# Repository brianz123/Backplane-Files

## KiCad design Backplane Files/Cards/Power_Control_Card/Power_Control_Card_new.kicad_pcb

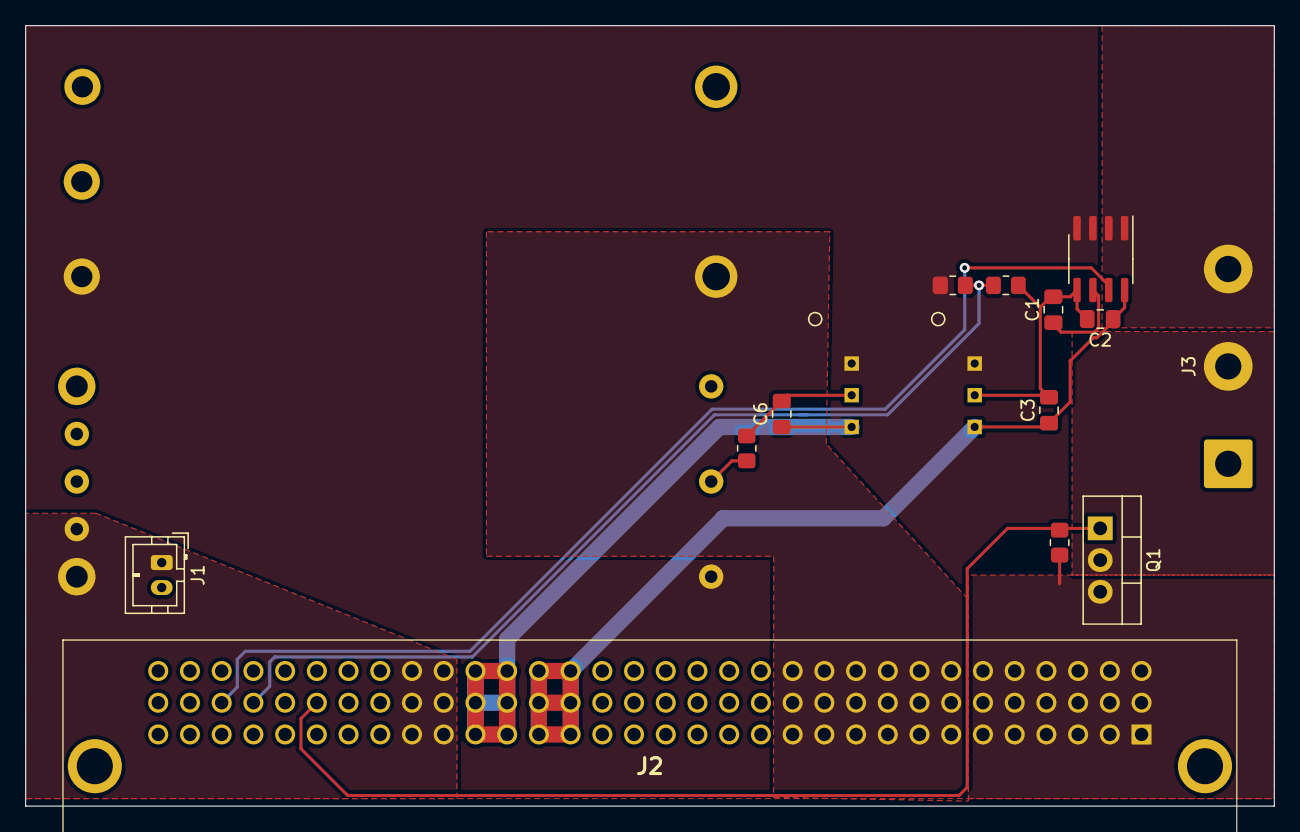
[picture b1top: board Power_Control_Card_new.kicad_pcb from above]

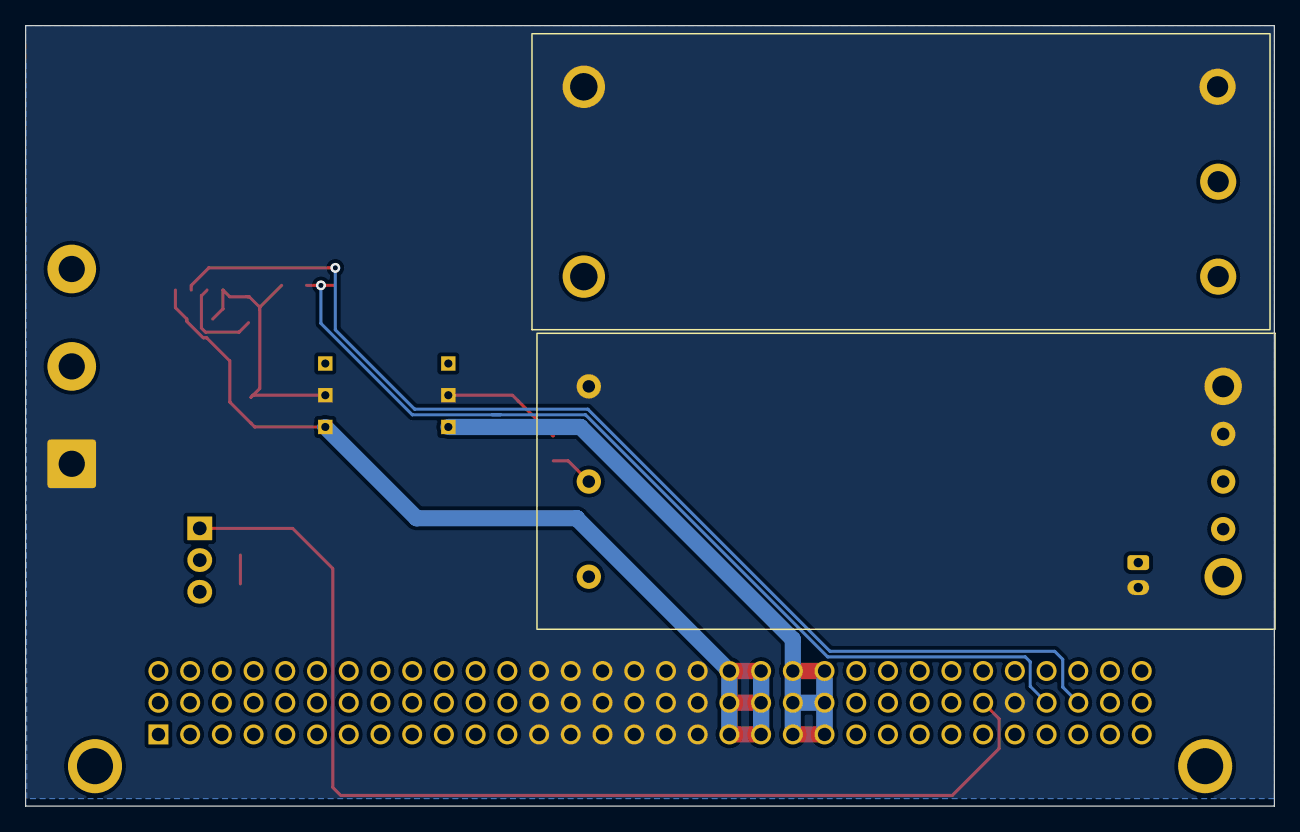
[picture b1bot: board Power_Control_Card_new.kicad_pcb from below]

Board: 2 copper layers, 100.0 x 62.5 mm, 17 parts (2 on the bottom side), 14 nets.

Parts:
C1: 47n; C_0805_2012Metric_Pad1.18x1.45mm_HandSolder
C2: 0.1u; C_0805_2012Metric_Pad1.18x1.45mm_HandSolder
C3, C6: 1u; C_0805_2012Metric_Pad1.18x1.45mm_HandSolder
DC/DC_CNVRT1: TSR2-2450; TSR2
DC/DC_CNVRT2: TSR2-2433; TSR2
INPT_CRRNT_SNSR1: TMCS1101A4B; SOIC-8_3.9x4.9mm_P1.27mm
J1: Conn_01x02; JST_PH_B2B-PH-K_1x02_P2.00mm_Vertical
J2: 6509475
J3: Conn_01x03_Pin; SolderWire-1.5sqmm_1x03_P7.8mm_D1.7mm_OD3.9mm
Q1: FQPF27P06; TO-220-3_Vertical
RSW1, RSW2: 10kO; R_0805_2012Metric_Pad1.20x1.40mm_HandSolder
U1: 240W_CONV
U2: 72W_CONV
VDIV1(R)1: 90kO; R_0805_2012Metric_Pad1.20x1.40mm_HandSolder
VDIV2(R)1: 10kO; R_0805_2012Metric_Pad1.20x1.40mm_HandSolder

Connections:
12V_Jetson: J1.1, J2.A23, J2.A24, J2.B23, J2.B24, J2.C23, J2.C24, U2.7 (SENSE+), U2.8 (VOUT)
+3.3V: C6.1, DC/DC_CNVRT2.3 (+V_OUT), J2.A21, J2.A22, J2.B21, J2.B22, J2.C21, J2.C22
+5V: C2.1, C3.1, DC/DC_CNVRT1.3 (+V_OUT), INPT_CRRNT_SNSR1.8 (VCC), J2.A19, J2.A20, J2.B19, J2.B20, J2.C19, J2.C20
+12V: J2.A7, J2.A8, J2.A9, J2.A10, J2.A11, J2.A12, J2.B7, J2.B8, J2.B9, J2.B10, J2.B11, J2.B12, J2.C7, J2.C8, J2.C9, J2.C10, J2.C11, J2.C12, U1.8 (VOUT)
+24V: J2.A1, J2.A2, J2.A3, J2.A4, J2.A5, J2.A6, J2.B1, J2.B2, J2.B3, J2.B4, J2.B5, J2.B6, J2.C1, J2.C2, J2.C3, J2.C4, J2.C5, J2.C6, Q1.3 (S), RSW1.1
/VBATT: INPT_CRRNT_SNSR1.1 (IP+), J3.3
/V_POWER: DC/DC_CNVRT1.1 (+V_IN), DC/DC_CNVRT2.1 (+V_IN), INPT_CRRNT_SNSR1.3 (IP-), U1.1 (VIN), U2.1 (VIN), VDIV1(R)1.1
DAT1: J2.B29, VDIV1(R)1.2, VDIV2(R)1.1
DAT2: INPT_CRRNT_SNSR1.7 (VIOUT), J2.B30
unnamed: C1.1, INPT_CRRNT_SNSR1.6 (FILTER)
unnamed: J3.2, Q1.2 (D)
unnamed: RSW2.1, U2.2 (ON/OFF)
SW1: C1.2, C2.2, C3.2, C6.2, DC/DC_CNVRT1.2 (GND), DC/DC_CNVRT2.2 (GND), INPT_CRRNT_SNSR1.5 (GND), J1.2, J2.A13, J2.A14, J2.A15, J2.A16, J2.A17, J2.A18, J2.B13, J2.B14, J2.B15, J2.B16, J2.B17, J2.B18, J2.B28, J2.C13, J2.C14, J2.C15, J2.C16, J2.C17, J2.C18, J3.1, RSW2.2, U1.3 (IN-), U1.4 (OUT-), U2.3 (IN-), U2.4 (OUT-), U2.5 (SENSE-), VDIV2(R)1.2
SW2: J2.B27, Q1.1 (G), RSW1.2

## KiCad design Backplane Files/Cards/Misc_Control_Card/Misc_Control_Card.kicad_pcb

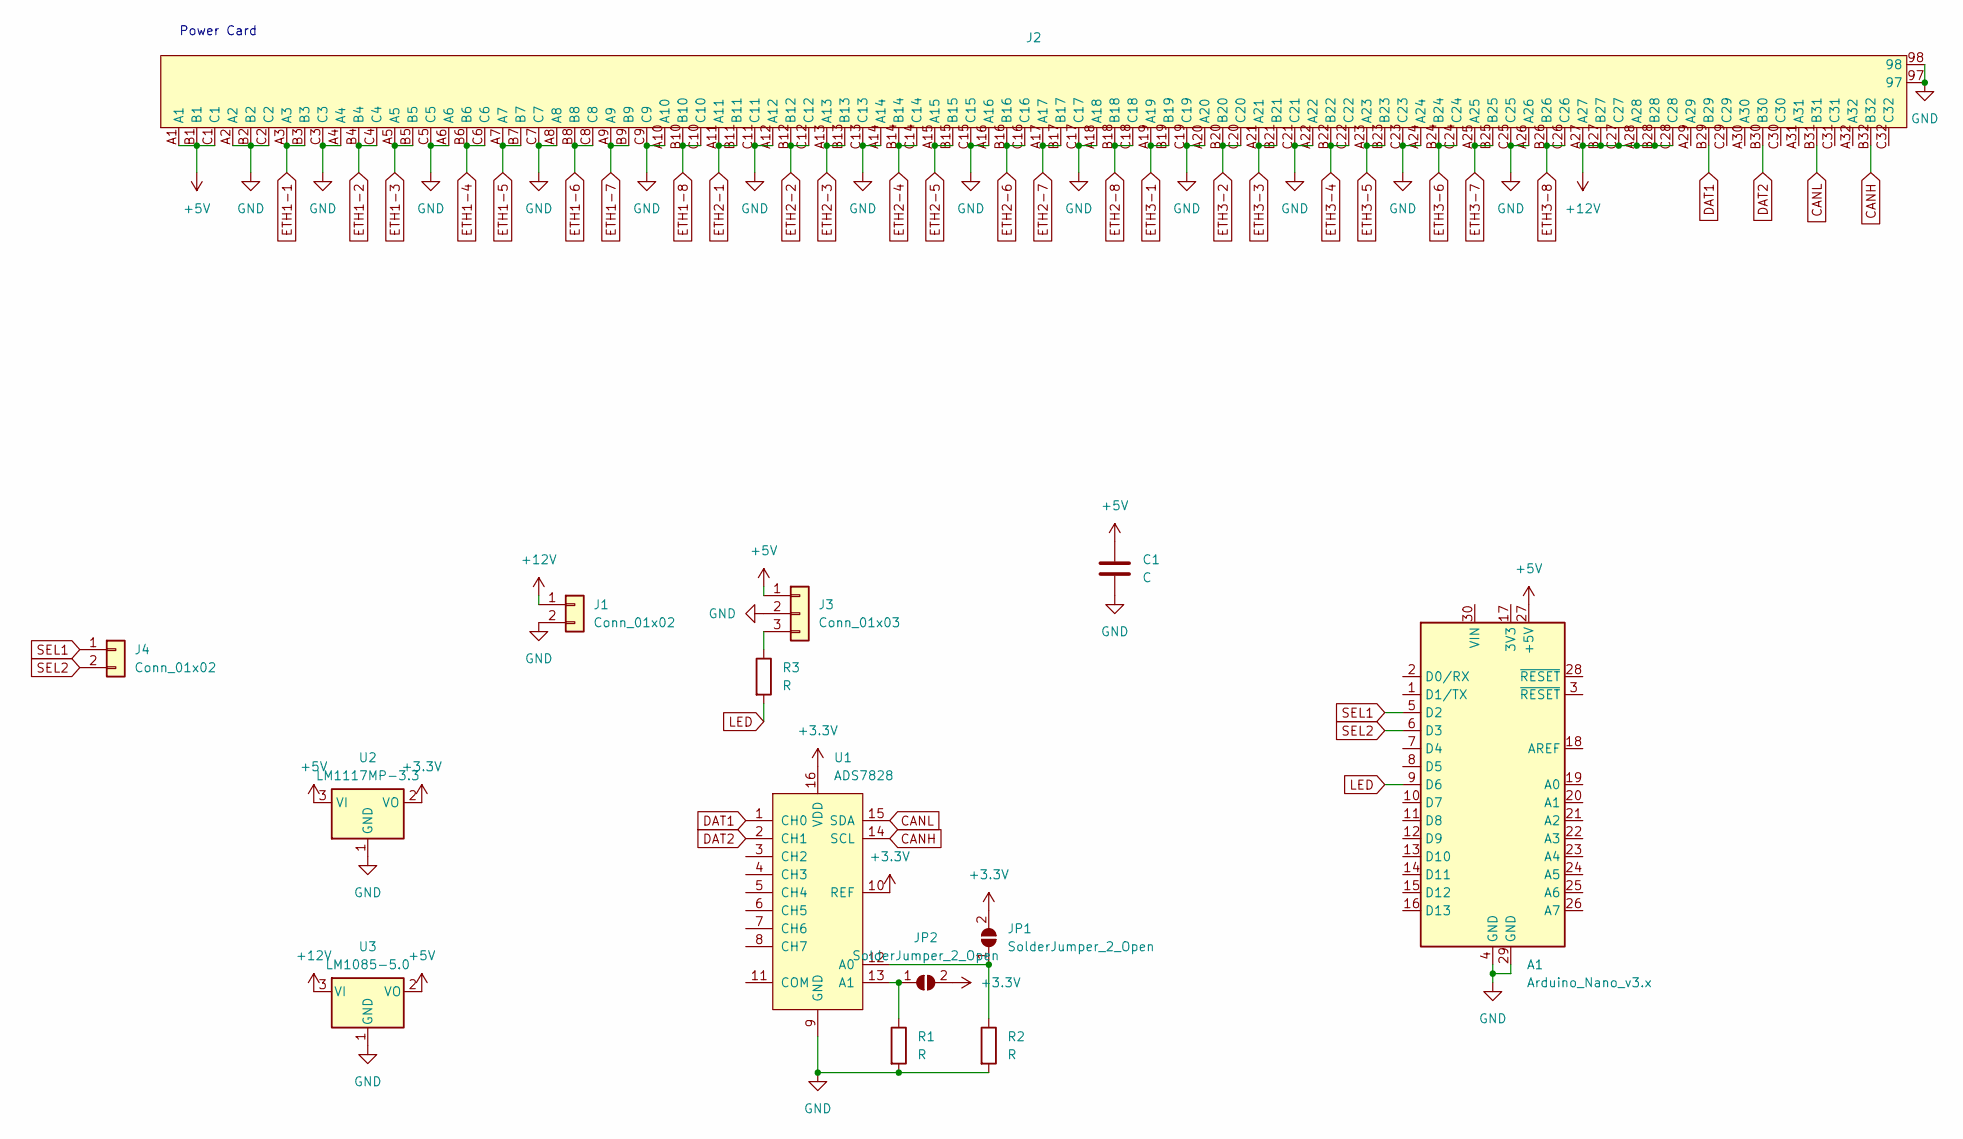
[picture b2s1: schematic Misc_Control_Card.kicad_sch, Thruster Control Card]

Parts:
A1: Arduino_Nano_v3.x; Arduino_Nano
C1: C; CP_Radial_D6.3mm_P2.50mm
J1, J4: Conn_01x02; PinHeader_1x02_P2.54mm_Vertical
J2: 6509475
J3: Conn_01x03; PinHeader_1x03_P2.54mm_Vertical
JP1, JP2: SolderJumper_2_Open; SolderJumper-2_P1.3mm_Open_TrianglePad1.0x1.5mm
R1, R2, R3: R; R_0805_2012Metric_Pad1.20x1.40mm_HandSolder
U1: ADS7828; TSSOP-16_4.4x5mm_P0.65mm
U2: LM1117MP-3.3; SOT-223-3_TabPin2
U3: LM1085-5.0; TO-220-3_Vertical

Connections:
+3.3V: JP1.2 (B), JP2.2 (B), U1.10 (REF), U1.16 (VDD), U2.2 (VO)
+5V: A1.27 (+5V), C1.1, J2.A1, J2.B1, J2.C1, J3.1, U2.3 (VI), U3.2 (VO)
+12V: J1.1, J2.A27, J2.A28, J2.B27, J2.B28, J2.C27, J2.C28, U3.3 (VI)
CANH: J2.B32, U1.14 (SCL)
CANL: J2.B31, U1.15 (SDA)
DAT1: J2.B29, U1.1 (CH0)
DAT2: J2.B30, U1.2 (CH1)
ETH1-1: J2.A3, J2.B3
ETH1-2: J2.B4, J2.C4
ETH1-3: J2.A5, J2.B5
ETH1-4: J2.B6, J2.C6
ETH1-5: J2.A7, J2.B7
ETH1-6: J2.B8, J2.C8
ETH1-7: J2.A9, J2.B9
ETH1-8: J2.B10, J2.C10
ETH2-1: J2.A11, J2.B11
ETH2-2: J2.B12, J2.C12
ETH2-3: J2.A13, J2.B13
ETH2-4: J2.B14, J2.C14
ETH2-5: J2.A15, J2.B15
ETH2-6: J2.B16, J2.C16
ETH2-7: J2.A17, J2.B17
ETH2-8: J2.B18, J2.C18
ETH3-1: J2.A19, J2.B19
ETH3-2: J2.B20, J2.C20
ETH3-3: J2.A21, J2.B21
ETH3-4: J2.B22, J2.C22
ETH3-5: J2.A23, J2.B23
ETH3-6: J2.B24, J2.C24
ETH3-7: J2.A25, J2.B25
ETH3-8: J2.B26, J2.C26
GND: A1.4 (GND), A1.29 (GND), C1.2, J1.2, J2.97, J2.98, J2.A2, J2.A4, J2.A6, J2.A8, J2.A10, J2.A12, J2.A14, J2.A16, J2.A18, J2.A20, J2.A22, J2.A24, J2.A26, J2.B2, J2.C2, J2.C3, J2.C5, J2.C7, J2.C9, J2.C11, J2.C13, J2.C15, J2.C17, J2.C19, J2.C21, J2.C23, J2.C25, J3.2, R1.2, R2.2, U1.9 (GND), U2.1 (GND), U3.1 (GND)
LED: A1.9 (D6), R3.2
unnamed: J3.3, R3.1
unnamed: JP1.1 (A), R2.1, U1.12 (A0)
unnamed: JP2.1 (A), R1.1, U1.13 (A1)
SEL1: A1.5 (D2), J4.1
SEL2: A1.6 (D3), J4.2

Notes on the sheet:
Power Card

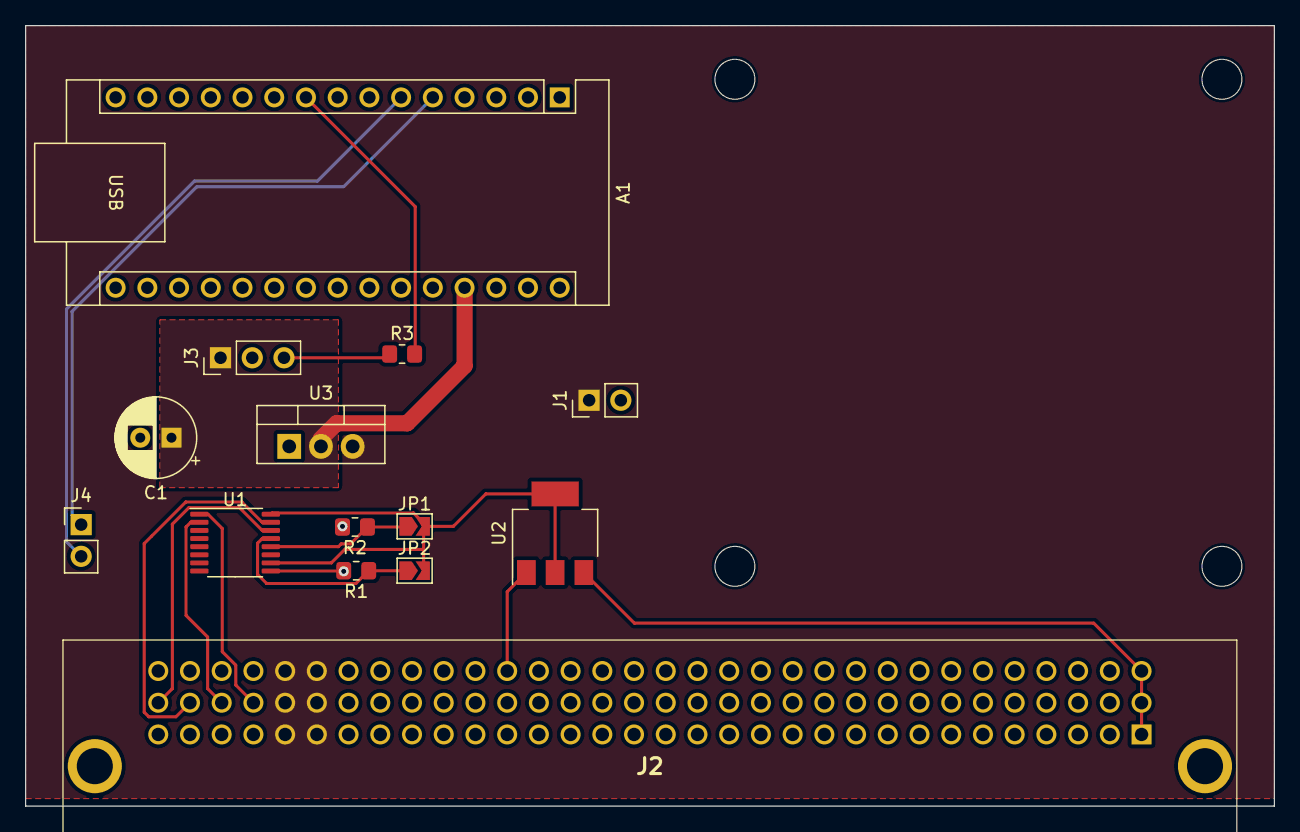
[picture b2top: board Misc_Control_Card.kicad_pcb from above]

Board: 2 copper layers, 100.0 x 62.5 mm, 14 parts (0 on the bottom side), 38 nets.

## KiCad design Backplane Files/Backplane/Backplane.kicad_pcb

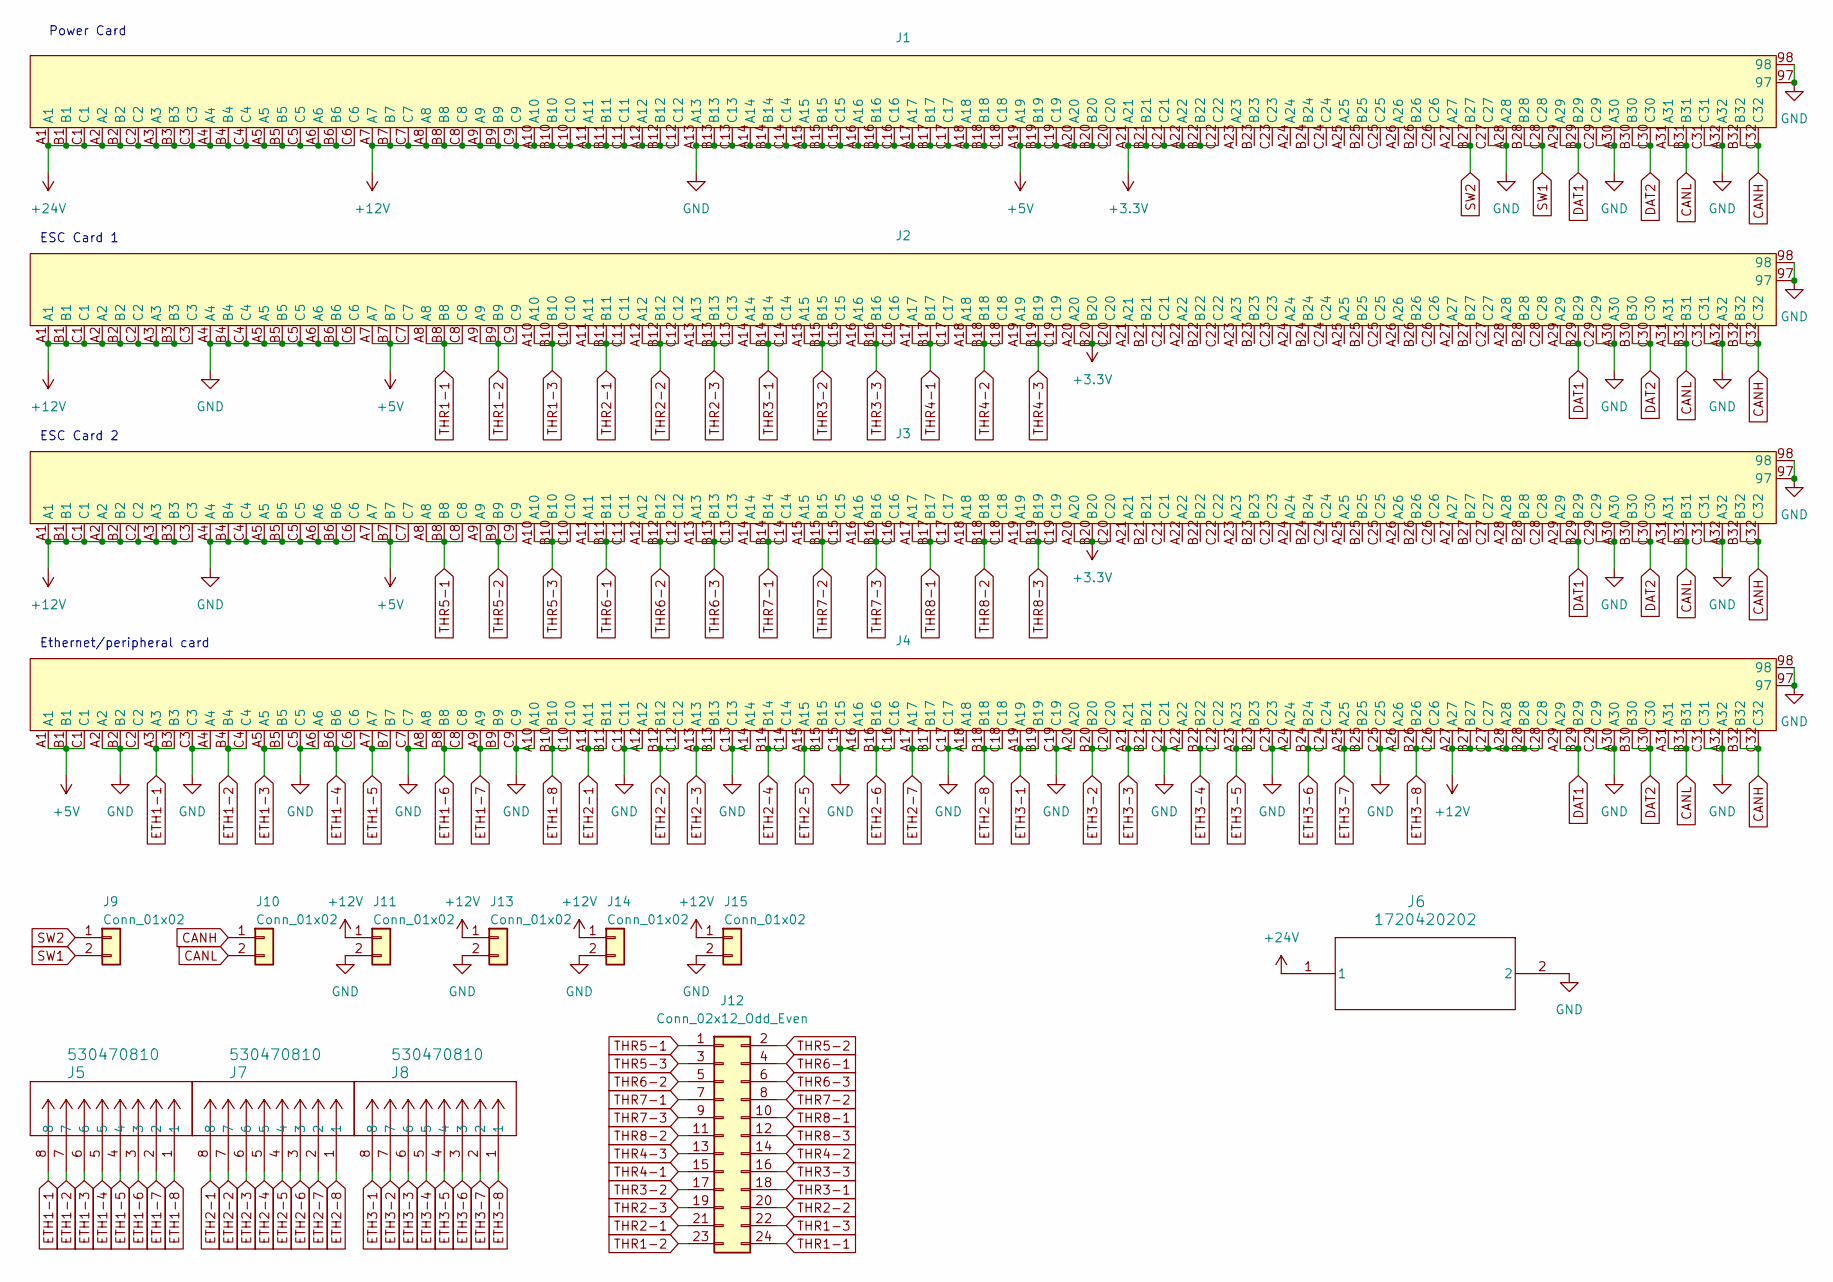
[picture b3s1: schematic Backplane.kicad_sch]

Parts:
J1, J2, J3, J4: CONN_650470-5_TYC
J5, J7, J8: 530470810; CON_530470810_MOL
J6: 1720420202; SUPERSABRE_2CIRCUIT
J9, J10, J11, J13, J14, J15: Conn_01x02; JST_PH_B2B-PH-K_1x02_P2.00mm_Vertical
J12: Conn_02x12_Odd_Even; Molex_Mini-Fit_Jr_5566-24A_2x12_P4.20mm_Vertical

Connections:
+3.3V: J1.A21, J1.A22, J1.B21, J1.B22, J1.C21, J1.C22, J2.A20, J2.B20, J2.C20, J3.A20, J3.B20, J3.C20
+5V: J1.A19, J1.A20, J1.B19, J1.B20, J1.C19, J1.C20, J2.A7, J2.B7, J2.C7, J3.A7, J3.B7, J3.C7, J4.A1, J4.B1, J4.C1
+12V: J1.A7, J1.A8, J1.A9, J1.A10, J1.A11, J1.A12, J1.B7, J1.B8, J1.B9, J1.B10, J1.B11, J1.B12, J1.C7, J1.C8, J1.C9, J1.C10, J1.C11, J1.C12, J2.A1, J2.A2, J2.A3, J2.B1, J2.B2, J2.B3, J2.C1, J2.C2, J2.C3, J3.A1, J3.A2, J3.A3, J3.B1, J3.B2, J3.B3, J3.C1, J3.C2, J3.C3, J4.A27, J4.A28, J4.B27, J4.B28, J4.C27, J4.C28, J11.1, J13.1, J14.1, J15.1
+24V: J1.A1, J1.A2, J1.A3, J1.A4, J1.A5, J1.A6, J1.B1, J1.B2, J1.B3, J1.B4, J1.B5, J1.B6, J1.C1, J1.C2, J1.C3, J1.C4, J1.C5, J1.C6, J6.1
CANH: J1.B32, J1.C32, J2.B32, J2.C32, J3.B32, J3.C32, J4.B32, J4.C32, J10.1
CANL: J1.A31, J1.B31, J2.A31, J2.B31, J3.A31, J3.B31, J4.A31, J4.B31, J10.2
DAT1: J1.A29, J1.B29, J2.A29, J2.B29, J3.A29, J3.B29, J4.A29, J4.B29
DAT2: J1.B30, J1.C30, J2.B30, J2.C30, J3.B30, J3.C30, J4.B30, J4.C30
ETH1-1: J4.A3, J4.B3, J5.8
ETH1-2: J4.B4, J4.C4, J5.7
ETH1-3: J4.A5, J4.B5, J5.6
ETH1-4: J4.B6, J4.C6, J5.5
ETH1-5: J4.A7, J4.B7, J5.4
ETH1-6: J4.B8, J4.C8, J5.3
ETH1-7: J4.A9, J4.B9, J5.2
ETH1-8: J4.B10, J4.C10, J5.1
ETH2-1: J4.A11, J4.B11, J7.8
ETH2-2: J4.B12, J4.C12, J7.7
ETH2-3: J4.A13, J4.B13, J7.6
ETH2-4: J4.B14, J4.C14, J7.5
ETH2-5: J4.A15, J4.B15, J7.4
ETH2-6: J4.B16, J4.C16, J7.3
ETH2-7: J4.A17, J4.B17, J7.2
ETH2-8: J4.B18, J4.C18, J7.1
ETH3-1: J4.A19, J4.B19, J8.8
ETH3-2: J4.B20, J4.C20, J8.7
ETH3-3: J4.A21, J4.B21, J8.6
ETH3-4: J4.B22, J4.C22, J8.5
ETH3-5: J4.A23, J4.B23, J8.4
ETH3-6: J4.B24, J4.C24, J8.3
ETH3-7: J4.A25, J4.B25, J8.2
ETH3-8: J4.B26, J4.C26, J8.1
GND: J1.97, J1.98, J1.A13, J1.A14, J1.A15, J1.A16, J1.A17, J1.A18, J1.A28, J1.A30, J1.A32, J1.B13, J1.B14, J1.B15, J1.B16, J1.B17, J1.B18, J1.C13, J1.C14, J1.C15, J1.C16, J1.C17, J1.C18, J1.C27, J1.C29, J1.C31, J2.97, J2.98, J2.A4, J2.A5, J2.A6, J2.A30, J2.A32, J2.B4, J2.B5, J2.B6, J2.C4, J2.C5, J2.C6, J2.C29, J2.C31, J3.97, J3.98, J3.A4, J3.A5, J3.A6, J3.A30, J3.A32, J3.B4, J3.B5, J3.B6, J3.C4, J3.C5, J3.C6, J3.C29, J3.C31, J4.97, J4.98, J4.A2, J4.A4, J4.A6, J4.A8, J4.A10, J4.A12, J4.A14, J4.A16, J4.A18, J4.A20, J4.A22, J4.A24, J4.A26, J4.A30, J4.A32, J4.B2, J4.C2, J4.C3, J4.C5, J4.C7, J4.C9, J4.C11, J4.C13, J4.C15, J4.C17, J4.C19, J4.C21, J4.C23, J4.C25, J4.C29, J4.C31, J6.2, J11.2, J13.2, J14.2, J15.2
SW1: J1.B28, J1.C28, J9.2
SW2: J1.A27, J1.B27, J9.1
THR1-1: J2.A8, J2.B8, J2.C8, J12.24
THR1-2: J2.A9, J2.B9, J2.C9, J12.23
THR1-3: J2.A10, J2.B10, J2.C10, J12.22
THR2-1: J2.A11, J2.B11, J2.C11, J12.21
THR2-2: J2.A12, J2.B12, J2.C12, J12.20
THR2-3: J2.A13, J2.B13, J2.C13, J12.19
THR3-1: J2.A14, J2.B14, J2.C14, J12.18
THR3-2: J2.A15, J2.B15, J2.C15, J12.17
THR3-3: J2.A16, J2.B16, J2.C16, J12.16
THR4-1: J2.A17, J2.B17, J2.C17, J12.15
THR4-2: J2.A18, J2.B18, J2.C18, J12.14
THR4-3: J2.A19, J2.B19, J2.C19, J12.13
THR5-1: J3.A8, J3.B8, J3.C8, J12.1
THR5-2: J3.A9, J3.B9, J3.C9, J12.2
THR5-3: J3.A10, J3.B10, J3.C10, J12.3
THR6-1: J3.A11, J3.B11, J3.C11, J12.4
THR6-2: J3.A12, J3.B12, J3.C12, J12.5
THR6-3: J3.A13, J3.B13, J3.C13, J12.6
THR7-1: J3.A14, J3.B14, J3.C14, J12.7
THR7-2: J3.A15, J3.B15, J3.C15, J12.8
THR7-3: J3.A16, J3.B16, J3.C16, J12.9
THR8-1: J3.A17, J3.B17, J3.C17, J12.10
THR8-2: J3.A18, J3.B18, J3.C18, J12.11
THR8-3: J3.A19, J3.B19, J3.C19, J12.12

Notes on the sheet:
ESC Card 1
Ethernet/peripheral card
Power Card
ESC Card 2

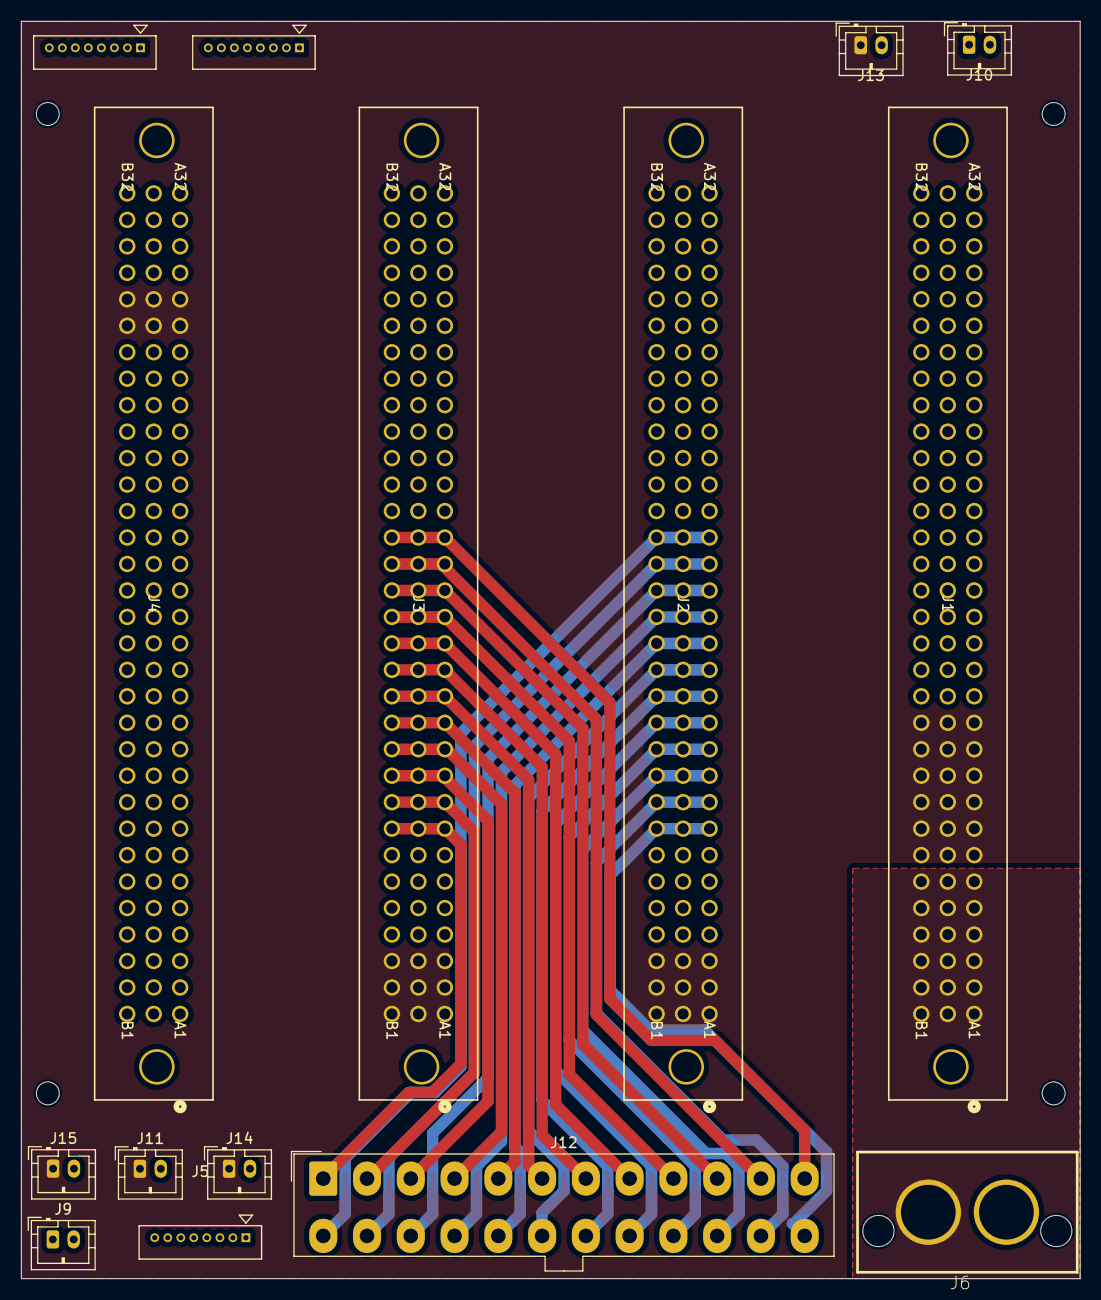
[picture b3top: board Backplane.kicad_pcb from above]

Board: 4 copper layers, 101.6 x 120.6 mm, 15 parts (0 on the bottom side), 59 nets.

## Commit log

2024-11-23 adding 3d models
2025-01-17 new power board
